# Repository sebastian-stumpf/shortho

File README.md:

# Shortho

Early prototype files. Please not that when ordering with JLC there will be two rotated parts.

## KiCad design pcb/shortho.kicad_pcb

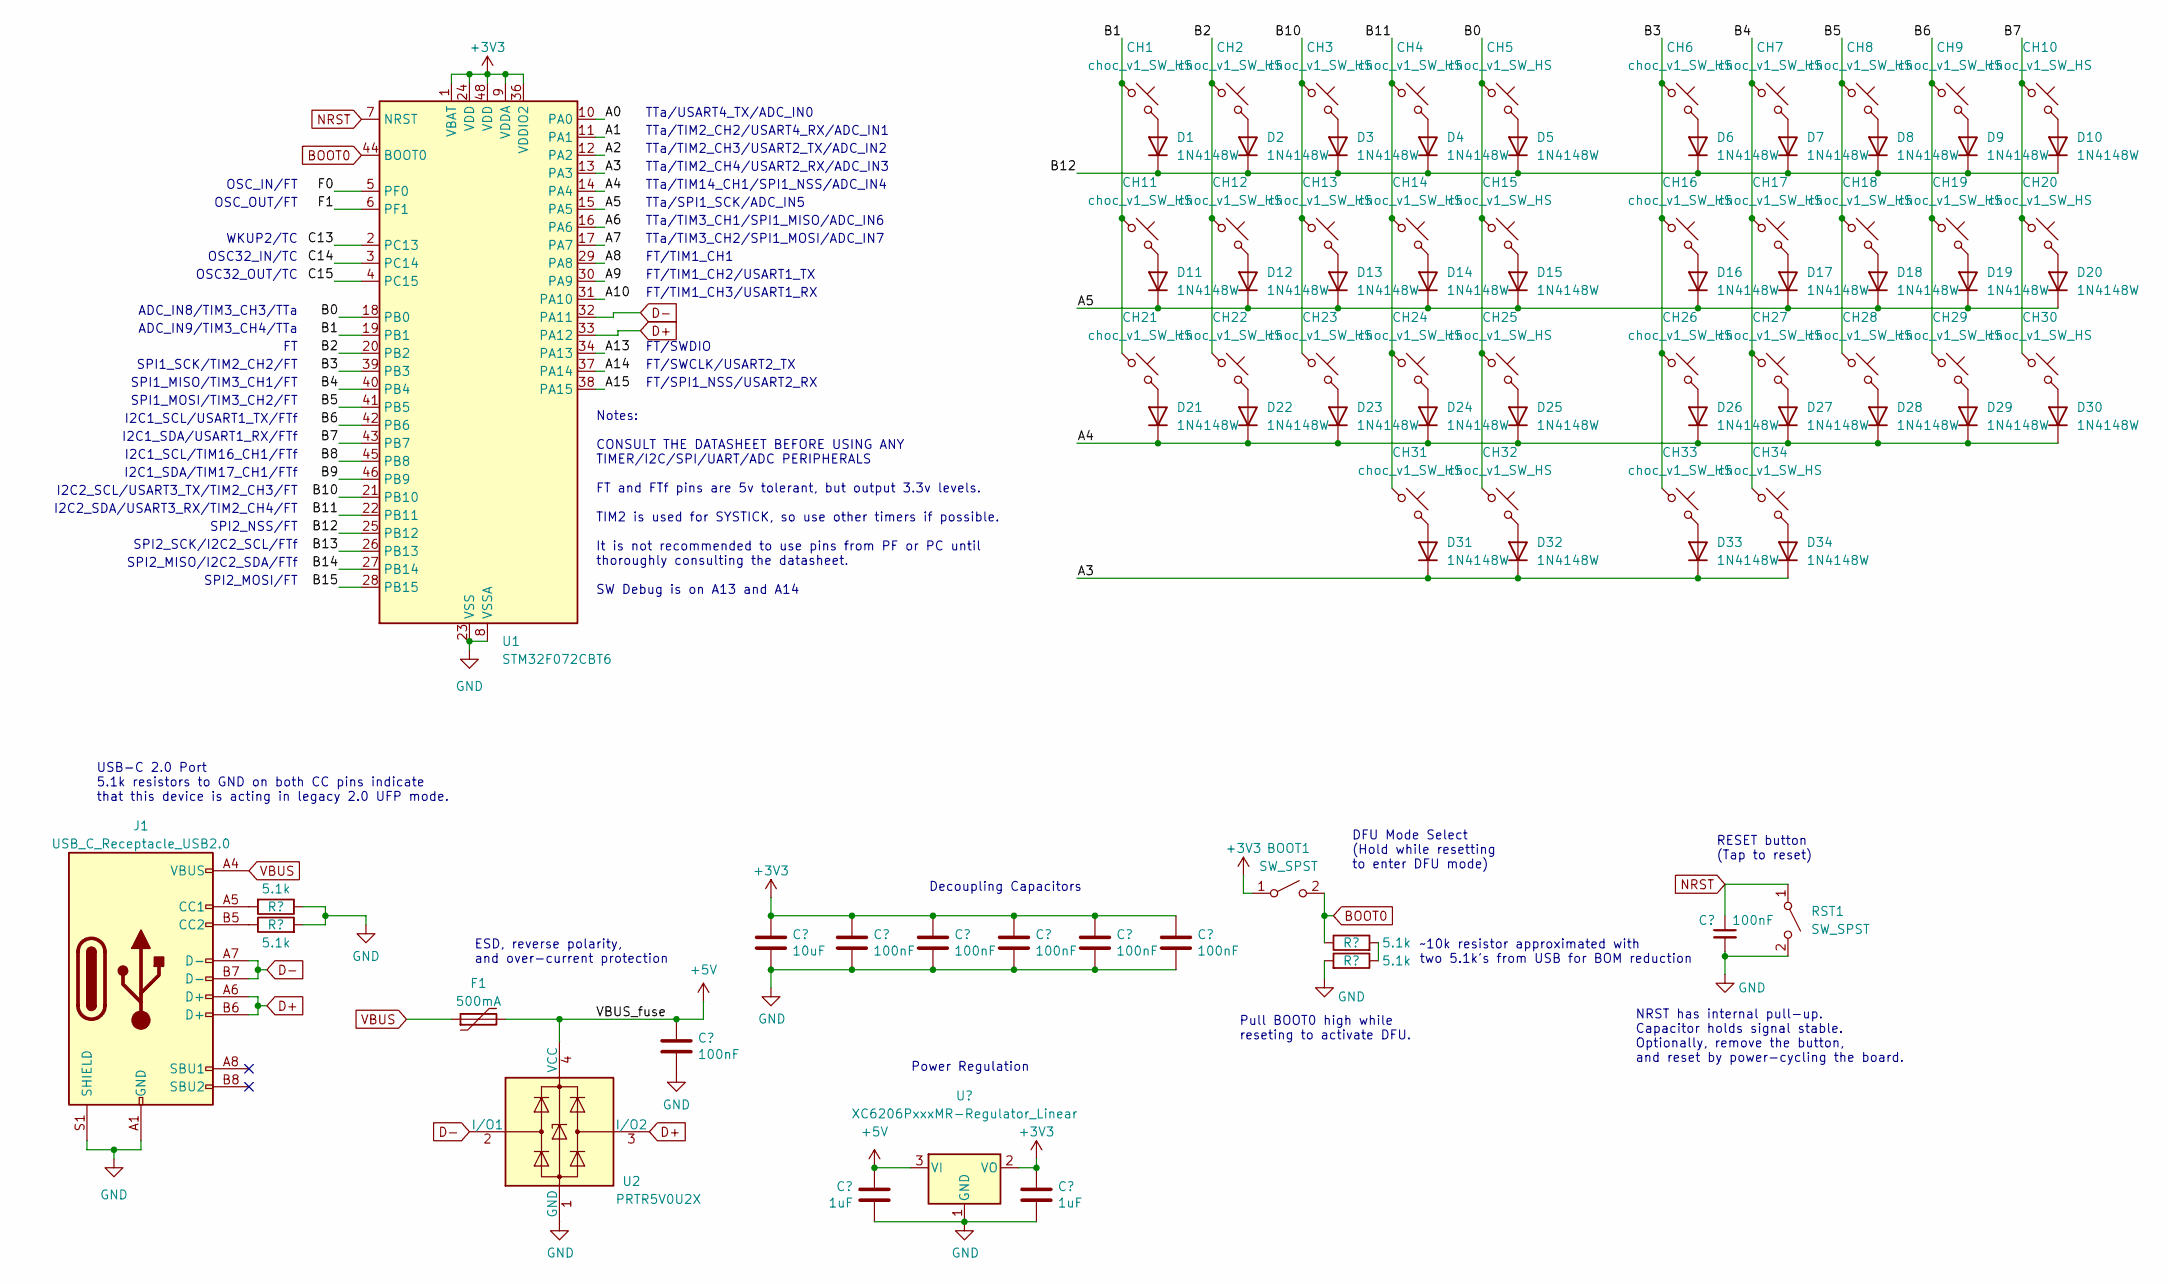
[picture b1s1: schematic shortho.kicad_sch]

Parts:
BOOT1: SW_SPST; SW_SPST_TL3342; LCSC C318884
C1, C3, C4, C5, C6, C7, C8: 100nF; C_0402_1005Metric; LCSC C307331
C2: 10uF; C_0603_1608Metric; LCSC C19702
C9, C10: 1uF; C_0402_1005Metric; LCSC C52923
CH1, CH2, CH3, CH4, CH5, CH6, CH7, CH8, CH9, CH10, CH11, CH12, CH13, CH14, CH15, CH16, CH17, CH18, CH19, CH20, CH21, CH22, CH23, CH24, CH25, CH26, CH27, CH28, CH29, CH30, CH31, CH34: choc_v1_SW_HS; SW_choc_v1_HS_CPG135001S30_1u; LCSC C5333465
CH32, CH33: choc_v1_SW_HS; SW_choc_v1_HS_CPG135001S30_1.5u; LCSC C5333465
D1, D2, D3, D4, D5, D6, D7, D8, D9, D10, D11, D12, D13, D14, D15, D16, D17, D18, D19, D20, D21, D22, D23, D24, D25, D26, D27, D28, D29, D30, D31, D32, D33, D34: 1N4148W; D_SOD-123; LCSC C81598
F1: 500mA; Fuse_1206_3216Metric; LCSC C135341
J1: USB_C_Receptacle_USB2.0; USB_C_Receptacle_HRO_TYPE-C-31-M-12; JlcRotOffset 180
R1, R2, R3, R4: 5.1k; R_0402_1005Metric; LCSC C25905
RST1: SW_SPST; SW_SPST_TL3342; LCSC C318884
U1: STM32F072CBT6; LQFP-48_7x7mm_P0.5mm; JlcRotOffset 90
U2: PRTR5V0U2X; SOT-143; LCSC C2827688
U3: XC6206PxxxMR-Regulator_Linear; SOT-23; LCSC C5446

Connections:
+3V3: BOOT1.1 (A), C2.1, C3.1, C4.1, C5.1, C6.1, C7.1, C10.1, U1.1 (VBAT), U1.9 (VDDA), U1.24 (VDD), U1.36 (VDDIO2), U1.48 (VDD), U3.2 (VO)
+5V: C8.1, C9.1, F1.2, U2.4 (VCC), U3.3 (VI)
/A0: U1.10 (PA0)
/A1: U1.11 (PA1)
/A2: U1.12 (PA2)
/A3: D31.1 (K), D32.1 (K), D33.1 (K), D34.1 (K), U1.13 (PA3)
/A4: D21.1 (K), D22.1 (K), D23.1 (K), D24.1 (K), D25.1 (K), D26.1 (K), D27.1 (K), D28.1 (K), D29.1 (K), D30.1 (K), U1.14 (PA4)
/A5: D11.1 (K), D12.1 (K), D13.1 (K), D14.1 (K), D15.1 (K), D16.1 (K), D17.1 (K), D18.1 (K), D19.1 (K), D20.1 (K), U1.15 (PA5)
/A6: U1.16 (PA6)
/A7: U1.17 (PA7)
/A8: U1.29 (PA8)
/A9: U1.30 (PA9)
/A10: U1.31 (PA10)
/A13: U1.34 (PA13)
/A14: U1.37 (PA14)
/A15: U1.38 (PA15)
/B0: CH5.1, CH15.1, CH25.1, CH32.1, U1.18 (PB0)
/B1: CH1.1, CH11.1, CH21.1, U1.19 (PB1)
/B2: CH2.1, CH12.1, CH22.1, U1.20 (PB2)
/B3: CH6.1, CH16.1, CH26.1, CH33.1, U1.39 (PB3)
/B4: CH7.1, CH17.1, CH27.1, CH34.1, U1.40 (PB4)
/B5: CH8.1, CH18.1, CH28.1, U1.41 (PB5)
/B6: CH9.1, CH19.1, CH29.1, U1.42 (PB6)
/B7: CH10.1, CH20.1, CH30.1, U1.43 (PB7)
/B8: U1.45 (PB8)
/B9: U1.46 (PB9)
/B10: CH3.1, CH13.1, CH23.1, U1.21 (PB10)
/B11: CH4.1, CH14.1, CH24.1, CH31.1, U1.22 (PB11)
/B12: D1.1 (K), D2.1 (K), D3.1 (K), D4.1 (K), D5.1 (K), D6.1 (K), D7.1 (K), D8.1 (K), D9.1 (K), D10.1 (K), U1.25 (PB12)
/B13: U1.26 (PB13)
/B14: U1.27 (PB14)
/B15: U1.28 (PB15)
/C13: U1.2 (PC13)
/C14: U1.3 (PC14)
/C15: U1.4 (PC15)
/F0: U1.5 (PF0)
/F1: U1.6 (PF1)
BOOT0: BOOT1.2 (B), R3.1, U1.44 (BOOT0)
D+: J1.A6 (D+), J1.B6 (D+), U1.33 (PA12), U2.3 (I/O2)
D-: J1.A7 (D-), J1.B7 (D-), U1.32 (PA11), U2.2 (I/O1)
GND: C1.2, C2.2, C3.2, C4.2, C5.2, C6.2, C7.2, C8.2, C9.2, C10.2, J1.A1 (GND), J1.A12 (GND), J1.B1 (GND), J1.B12 (GND), J1.S1 (SHIELD), R1.1, R2.2, R4.2, RST1.2 (B), U1.8 (VSSA), U1.23 (VSS), U1.35 (VSS), U1.47 (VSS), U2.1 (GND), U3.1 (GND)
NRST: C1.1, RST1.1 (A), U1.7 (NRST)
unnamed: CH1.2, D1.2 (A)
unnamed: CH2.2, D2.2 (A)
unnamed: CH3.2, D3.2 (A)
unnamed: CH4.2, D4.2 (A)
unnamed: CH5.2, D5.2 (A)
unnamed: CH6.2, D6.2 (A)
unnamed: CH7.2, D7.2 (A)
unnamed: CH8.2, D8.2 (A)
unnamed: CH9.2, D9.2 (A)
unnamed: CH10.2, D10.2 (A)
unnamed: CH11.2, D11.2 (A)
unnamed: CH12.2, D12.2 (A)
unnamed: CH13.2, D13.2 (A)
unnamed: CH14.2, D14.2 (A)
unnamed: CH15.2, D15.2 (A)
unnamed: CH16.2, D16.2 (A)
unnamed: CH17.2, D17.2 (A)
unnamed: CH18.2, D18.2 (A)
unnamed: CH19.2, D19.2 (A)
unnamed: CH20.2, D20.2 (A)
unnamed: CH21.2, D21.2 (A)
unnamed: CH22.2, D22.2 (A)
unnamed: CH23.2, D23.2 (A)
unnamed: CH24.2, D24.2 (A)
unnamed: CH25.2, D25.2 (A)
unnamed: CH26.2, D26.2 (A)
unnamed: CH27.2, D27.2 (A)
unnamed: CH28.2, D28.2 (A)
unnamed: CH29.2, D29.2 (A)
unnamed: CH30.2, D30.2 (A)
unnamed: CH31.2, D31.2 (A)
unnamed: CH32.2, D32.2 (A)
unnamed: CH33.2, D33.2 (A)
unnamed: CH34.2, D34.2 (A)
unnamed: J1.A5 (CC1), R1.2
unnamed: J1.B5 (CC2), R2.1
unnamed: R3.2, R4.1
VBUS: F1.1, J1.A4 (VBUS), J1.A9 (VBUS), J1.B4 (VBUS), J1.B9 (VBUS)

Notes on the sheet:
SPI1_SCK/TIM2_CH2/FT
FT/TIM1_CH1
FT/TIM1_CH3/USART1_RX
SPI2_NSS/FT
Notes: CONSULT THE DATASHEET BEFORE USING ANY TIMER/I2C/SPI/UART/ADC PERIPHERALS FT and FTf pins are 5v tolerant, but output 3.3v levels. TIM2 is used for SYSTICK, so use other timers if possible. It is not recommended to use pins from PF or PC until thoroughly consulting the datasheet. SW Debug is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
TTa/TIM2_CH4/USART2_RX/ADC_IN3
NRST has internal pull-up. Capacitor holds signal stable. Optionally, remove the button, and reset by power-cycling the board.
FT/SWDIO
Decoupling Capacitors
SPI1_MOSI/TIM3_CH2/FT
ADC_IN9/TIM3_CH4/TTa
I2C2_SCL/USART3_TX/TIM2_CH3/FT
SPI2_MISO/I2C2_SDA/FTf
FT/SWCLK/USART2_TX
I2C1_SCL/TIM16_CH1/FTf
~10k resistor approximated with two 5.1k's from USB for BOM reduction
TTa/TIM2_CH2/USART4_RX/ADC_IN1
USB-C 2.0 Port 5.1k resistors to GND on both CC pins indicate that this device is acting in legacy 2.0 UFP mode.
TTa/TIM2_CH3/USART2_TX/ADC_IN2
OSC_IN/FT
DFU Mode Select (Hold while resetting to enter DFU mode)
WKUP2/TC
I2C2_SDA/USART3_RX/TIM2_CH4/FT
ADC_IN8/TIM3_CH3/TTa
RESET button (Tap to reset)
Pull BOOT0 high while reseting to activate DFU.
I2C1_SDA/TIM17_CH1/FTf
TTa/SPI1_SCK/ADC_IN5
TTa/TIM3_CH1/SPI1_MISO/ADC_IN6
TTa/TIM3_CH2/SPI1_MOSI/ADC_IN7
OSC32_OUT/TC
FT/SPI1_NSS/USART2_RX
SPI1_MISO/TIM3_CH1/FT
OSC32_IN/TC
TTa/TIM14_CH1/SPI1_NSS/ADC_IN4
I2C1_SDA/USART1_RX/FTf
SPI2_MOSI/FT
FT/TIM1_CH2/USART1_TX
Power Regulation
SPI2_SCK/I2C2_SCL/FTf

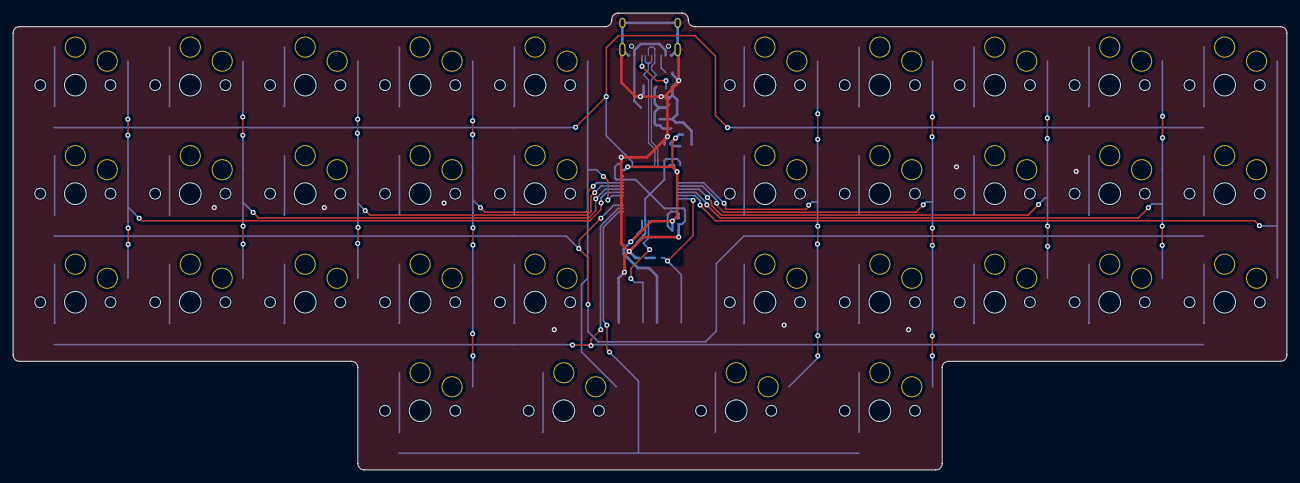
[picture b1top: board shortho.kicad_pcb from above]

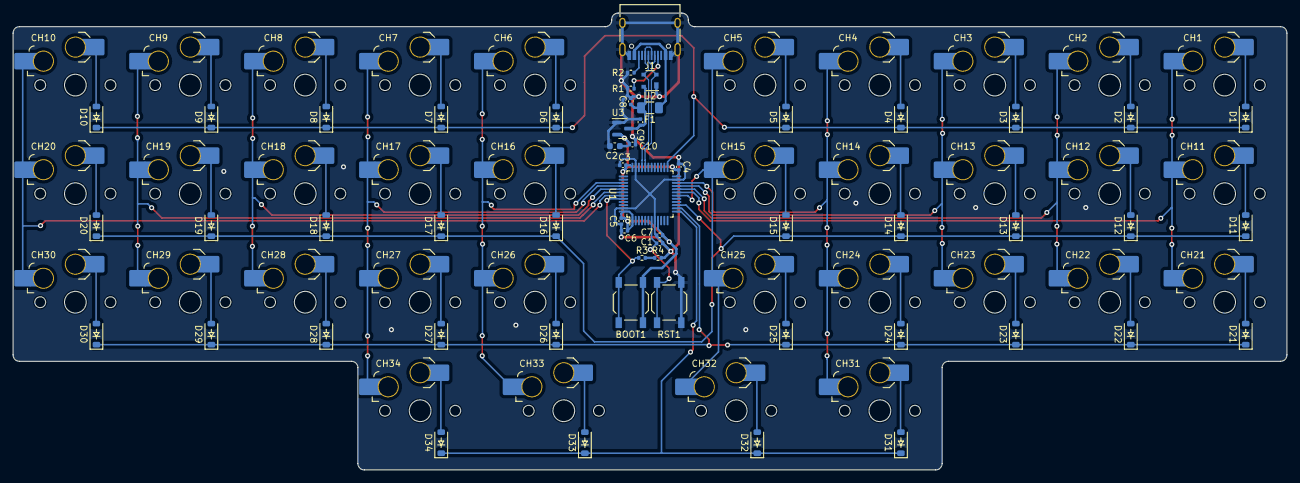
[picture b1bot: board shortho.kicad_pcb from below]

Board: 2 copper layers, 199.5 x 71.5 mm, 89 parts (89 on the bottom side), 59 nets.
